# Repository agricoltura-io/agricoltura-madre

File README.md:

# agricoltura-madre
Wired and Wireless gateway for all Agricoltura sensors/module supports RS485, Sub1GHZ, and 2.4GHZ networks

Quick Specs:

Beaglebone Green Based Version - Cape
- Seeedstudio Beaglebone Green
- 2x RS485 ports
- Sub 1GHZ wirless modem with SMA Antenna Connector
- 2.4GHZ wireless modem with SMA Antenna connector, supporting all 2.4G types
- WiFi modem with SMA antenna connector
- 1x USB 2.0 ports
- USB serial monitor connection
- Ethernet

Beaglebone SiP Based Version
- OSD335x Family System-in-package, running Debian Linux
- 4x RS485 ports
- Sub 1GHZ wirless modem with SMA Antenna Connector
- 2.4GHZ wireless model with SMA Antenna connector, supporting all 2.4G types
- WiFi modem with SMA antenna connector
- 2X USB 2.0 ports
- USB serial monitor connection
- Ethernet

Raspberry Pi 4 based version:
- 2x RS485 ports
- Sub 1GHZ wirless modem with SMA Antenna Connector
- 2.4GHZ wireless model with SMA Antenna connector, supporting all 2.4G types
- Integrated WiFi (RPi4)
- USB ports (RPi4)
- Ethernet
- PoE or 24VAC Power

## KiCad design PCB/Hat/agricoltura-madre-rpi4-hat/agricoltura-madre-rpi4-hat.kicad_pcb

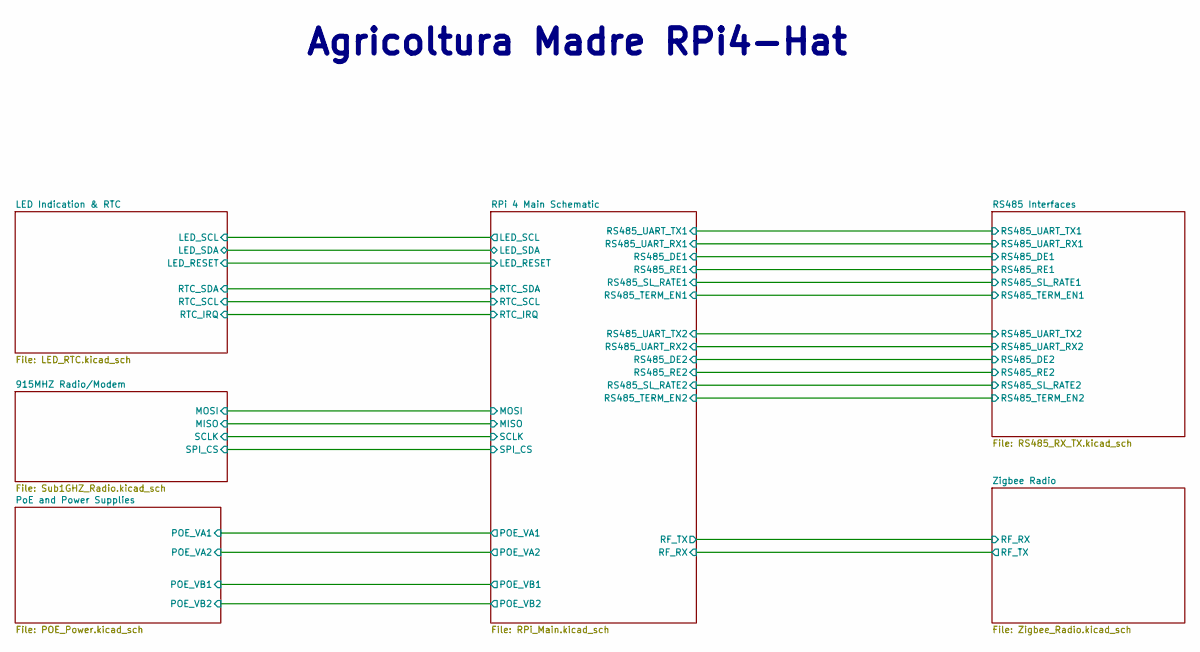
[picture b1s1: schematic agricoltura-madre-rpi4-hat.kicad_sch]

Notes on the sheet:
Agricoltura Madre RPi4-Hat

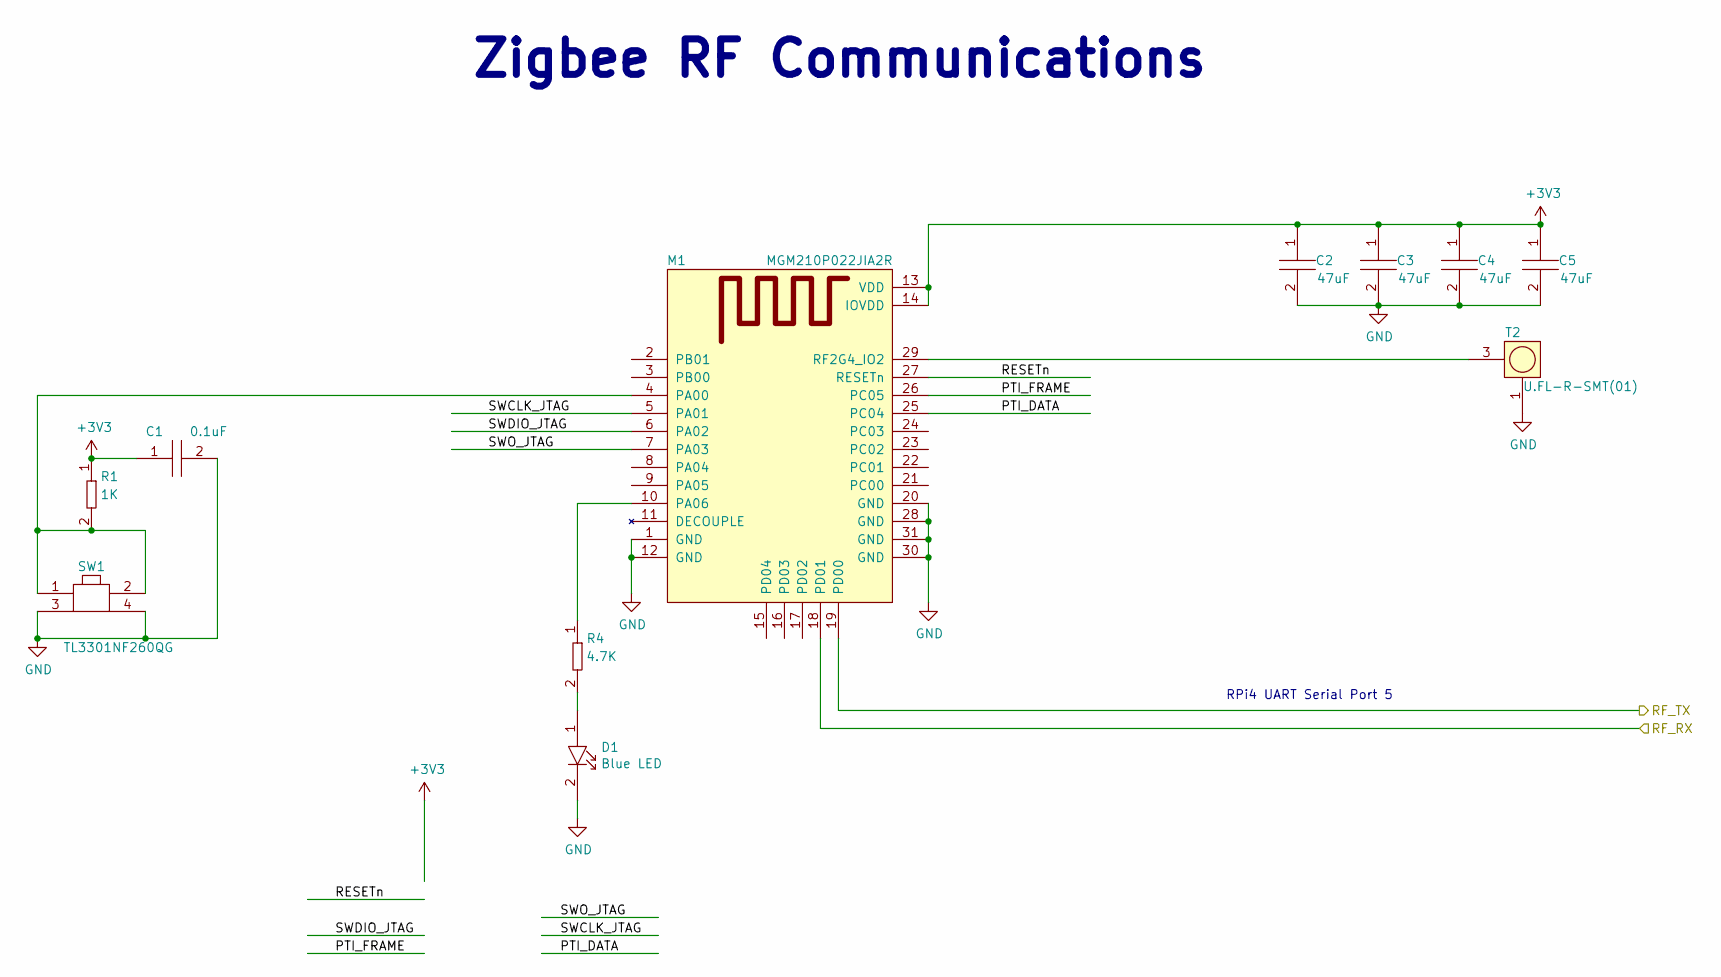
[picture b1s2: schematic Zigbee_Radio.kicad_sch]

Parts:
C1: GRM155R71E104KE14J; C0402; Tolerance 10%; Voltage 25V; MFR# GRM155R71E104KE14J
C2, C3, C4, C5: GRM188R60J476ME15D; C0603; Tolerance 20%; Voltage 6.3V; MFR# GRM188R60J476ME15D
D1: LTST-C194TBKT; LED0603; Tolerance *; Voltage 3.3V; MFR# LTST-C194TBKT
M1: MGM210P022JIA2R; Tolerance *; Voltage 1.8V-3.8V; MFR# MGM210P022JIA2R
R1: RC0402FR-071KL; R0402; Tolerance 1%; Voltage *; MFR# RC0402FR-071KL
R4: RC0402FR-074K7L; R0402; Tolerance 1%; Voltage *; MFR# RC0402FR-074K7L
SW1: TL3301NF260QG; Tolerance *; Voltage 12VDC; MFR# TL3301NF260QG
T2: U.FL-R-SMT(01); HRS_U.FL-R-SMT; Tolerance *; Voltage 3.3V; MFR# U.FL-R-SMT(01)

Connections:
+3V3: C1.1, C2.1, C3.1, C4.1, C5.1, M1.13 (VDD), M1.14 (IOVDD), R1.1; also elsewhere on the board
/RPi 4 Main Schematic/RF_RX: M1.19 (PD00); also elsewhere on the board
/Zigbee Radio /PTI_DATA: M1.25 (PC04)
/Zigbee Radio /PTI_FRAME: M1.26 (PC05)
/Zigbee Radio /RESETn: M1.27 (RESETn)
/Zigbee Radio /RF_RX: M1.18 (PD01); also elsewhere on the board
/Zigbee Radio /SWCLK_JTAG: M1.5 (PA01)
/Zigbee Radio /SWDIO_JTAG: M1.6 (PA02)
/Zigbee Radio /SWO_JTAG: M1.7 (PA03)
GND: C1.2, C2.2, C3.2, C4.2, C5.2, D1.2, M1.1 (GND), M1.12 (GND), M1.20 (GND), M1.28 (GND), M1.30 (GND), M1.31 (GND), SW1.3, SW1.4, T2.1; also elsewhere on the board
unnamed: D1.1, R4.2
unnamed: M1.4 (PA00), R1.2, SW1.1, SW1.2
unnamed: M1.10 (PA06), R4.1
unnamed: M1.29 (RF2G4_IO2), T2.3

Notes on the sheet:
Zigbee RF Communications
RPi4 UART Serial Port 5

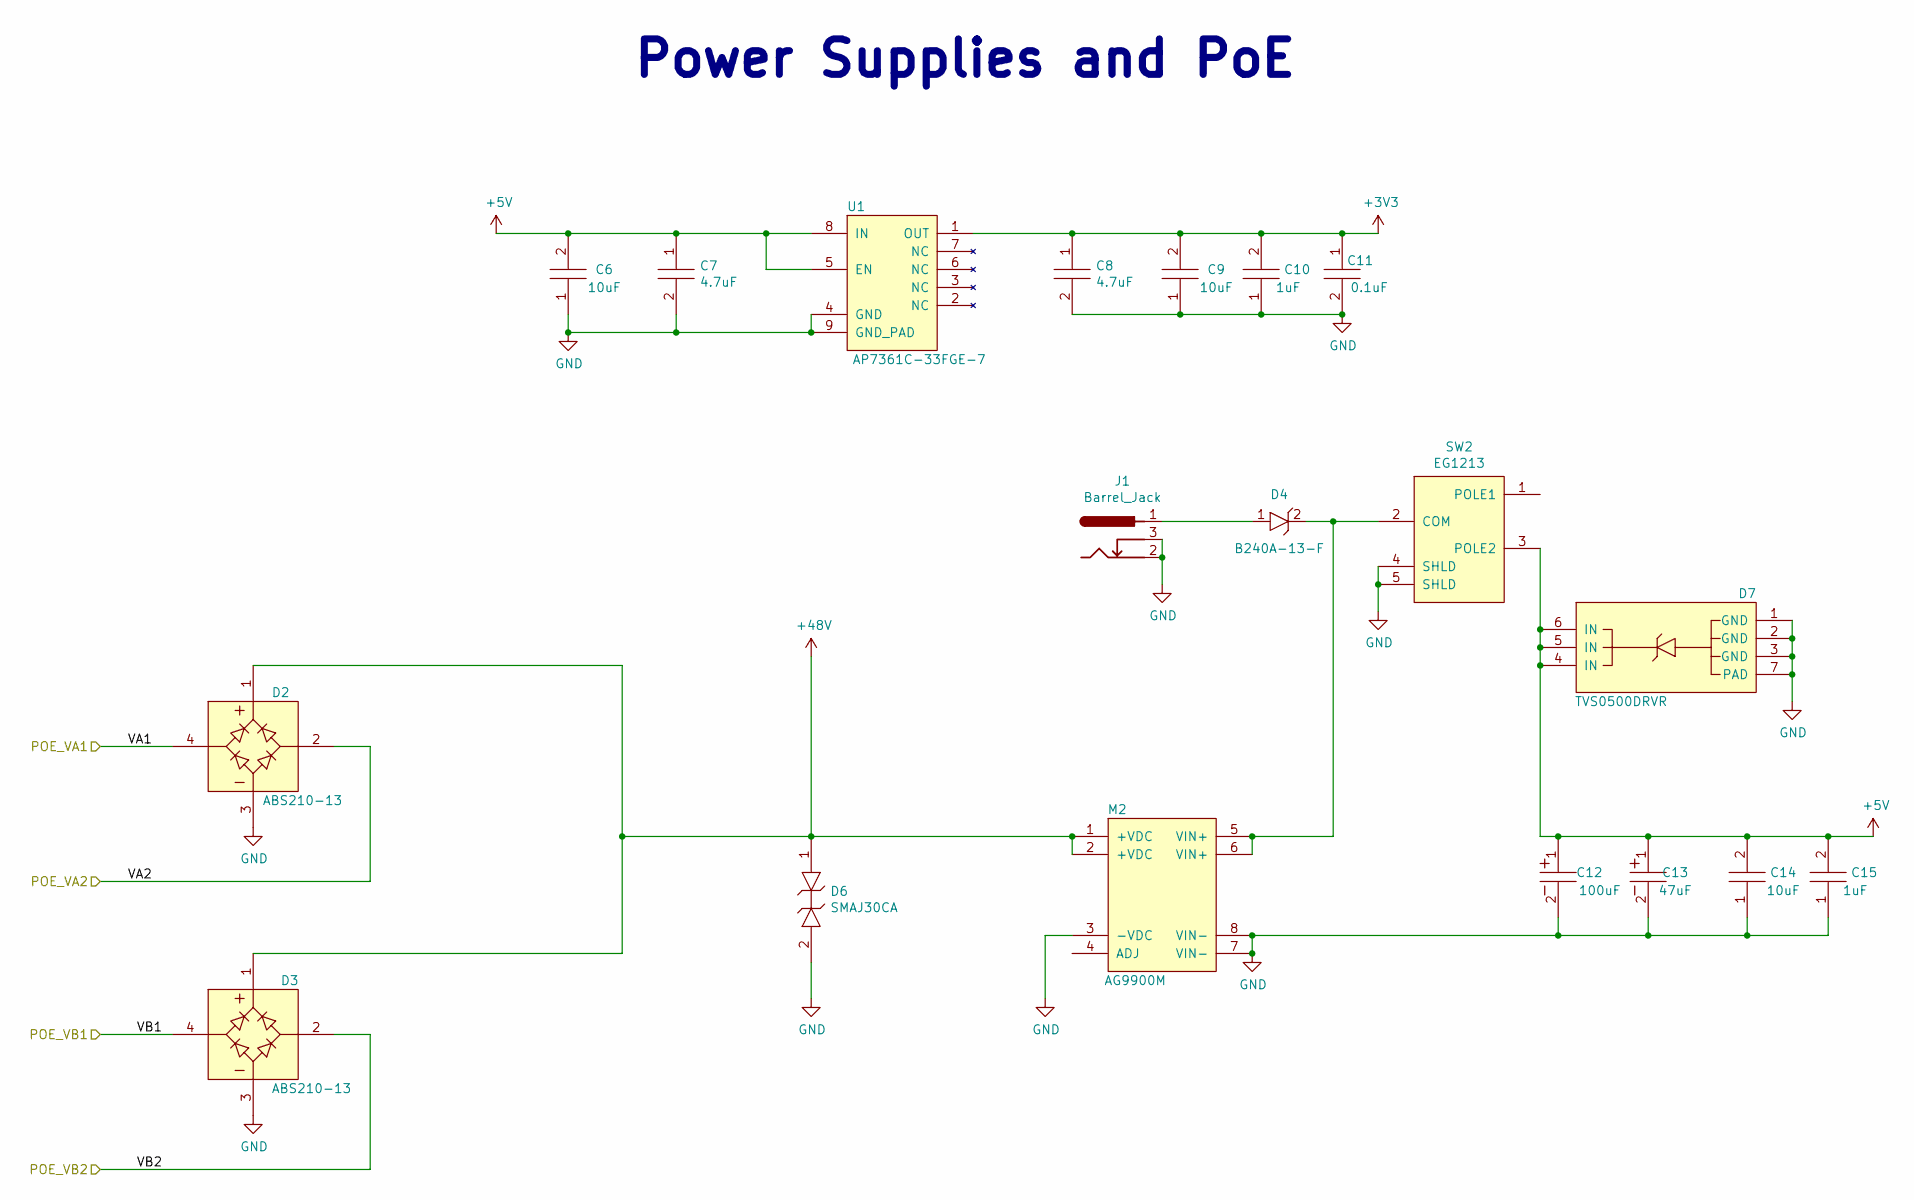
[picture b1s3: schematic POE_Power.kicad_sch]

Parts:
C6, C9, C14: GRM188R61A106KE69J; C0603; Tolerance 10%; Voltage 10V; MFR# GRM188R61A106KE69J
C7, C8: GRM155R61A475MEAAD; C0402; Tolerance 20%; Voltage 10V; MFR# GRM155R61A475MEAAD
C10, C15: GRM155C81A105KA12D; C0402; Tolerance 10%; Voltage 10V; MFR# GRM155C81A105KA12D
C11: GRM155R71E104KE14J; C0402; Tolerance 10%; Voltage 25V; MFR# GRM155R71E104KE14J
C12: UUX1J101MNL1GS; Tolerance 20%; Voltage 63V; MFR# UUX1J101MNL1GS
C13: UWT1H470MCL1GS; Tolerance 20%; Voltage 63V; MFR# UWT1H470MCL1GS
D2, D3: ABS210-13; Tolerance *; Voltage 1KV 2A; MFR# ABS210-13
D4: B240A-13-F; Tolerance *; Voltage 40V; MFR# B240A-13-F
D6: SMAJ30CA; Tolerance *; Voltage 48.4V; MFR# SMAJ30CA
D7: TVS0500DRVR; Tolerance *; Voltage 5V; MFR# TVS0500DRVR
J1: Barrel_Jack; BARREL_JACK
M2: AG9900M; 9900M_POE; Tolerance *; Voltage *; MFR# *
SW2: EG1213; SW_EG1213; Tolerance *; Voltage 30V; MFR# EG1213
U1: AP7361C-33FGE-7; DFN3030-8; Tolerance *; Voltage 6VIN MAX 3.3V out; MFR# AP7361C-33FGE-7

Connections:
+3V3: C8.1, C9.2, C10.2, C11.1, U1.1 (OUT); also elsewhere on the board
+5V: C6.2, C7.1, C12.1, C13.1, C14.2, C15.2, D7.4 (IN), D7.5 (IN), D7.6 (IN), SW2.3 (POLE2), U1.5 (EN), U1.8 (IN); also elsewhere on the board
+48V: D2.1, D3.1, D6.1, M2.1 (+VDC), M2.2 (+VDC)
/PoE and Power Supplies/POE_VA1: D2.4; also elsewhere on the board
/PoE and Power Supplies/POE_VA2: D2.2; also elsewhere on the board
/PoE and Power Supplies/POE_VB1: D3.4; also elsewhere on the board
/PoE and Power Supplies/POE_VB2: D3.2; also elsewhere on the board
GND: C6.1, C7.2, C8.2, C9.1, C10.1, C11.2, C12.2, C13.2, C14.1, C15.1, D2.3, D3.3, D6.2, D7.1 (GND), D7.2 (GND), D7.3 (GND), D7.7 (PAD), J1.2, J1.3, M2.3 (-VDC), M2.7 (VIN-), M2.8 (VIN-), SW2.4 (SHLD), SW2.5 (SHLD), U1.4 (GND), U1.9 (GND_PAD); also elsewhere on the board
unnamed: D4.1, J1.1
unnamed: D4.2, M2.5 (VIN+), M2.6 (VIN+), SW2.2 (COM)

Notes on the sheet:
Power Supplies and PoE

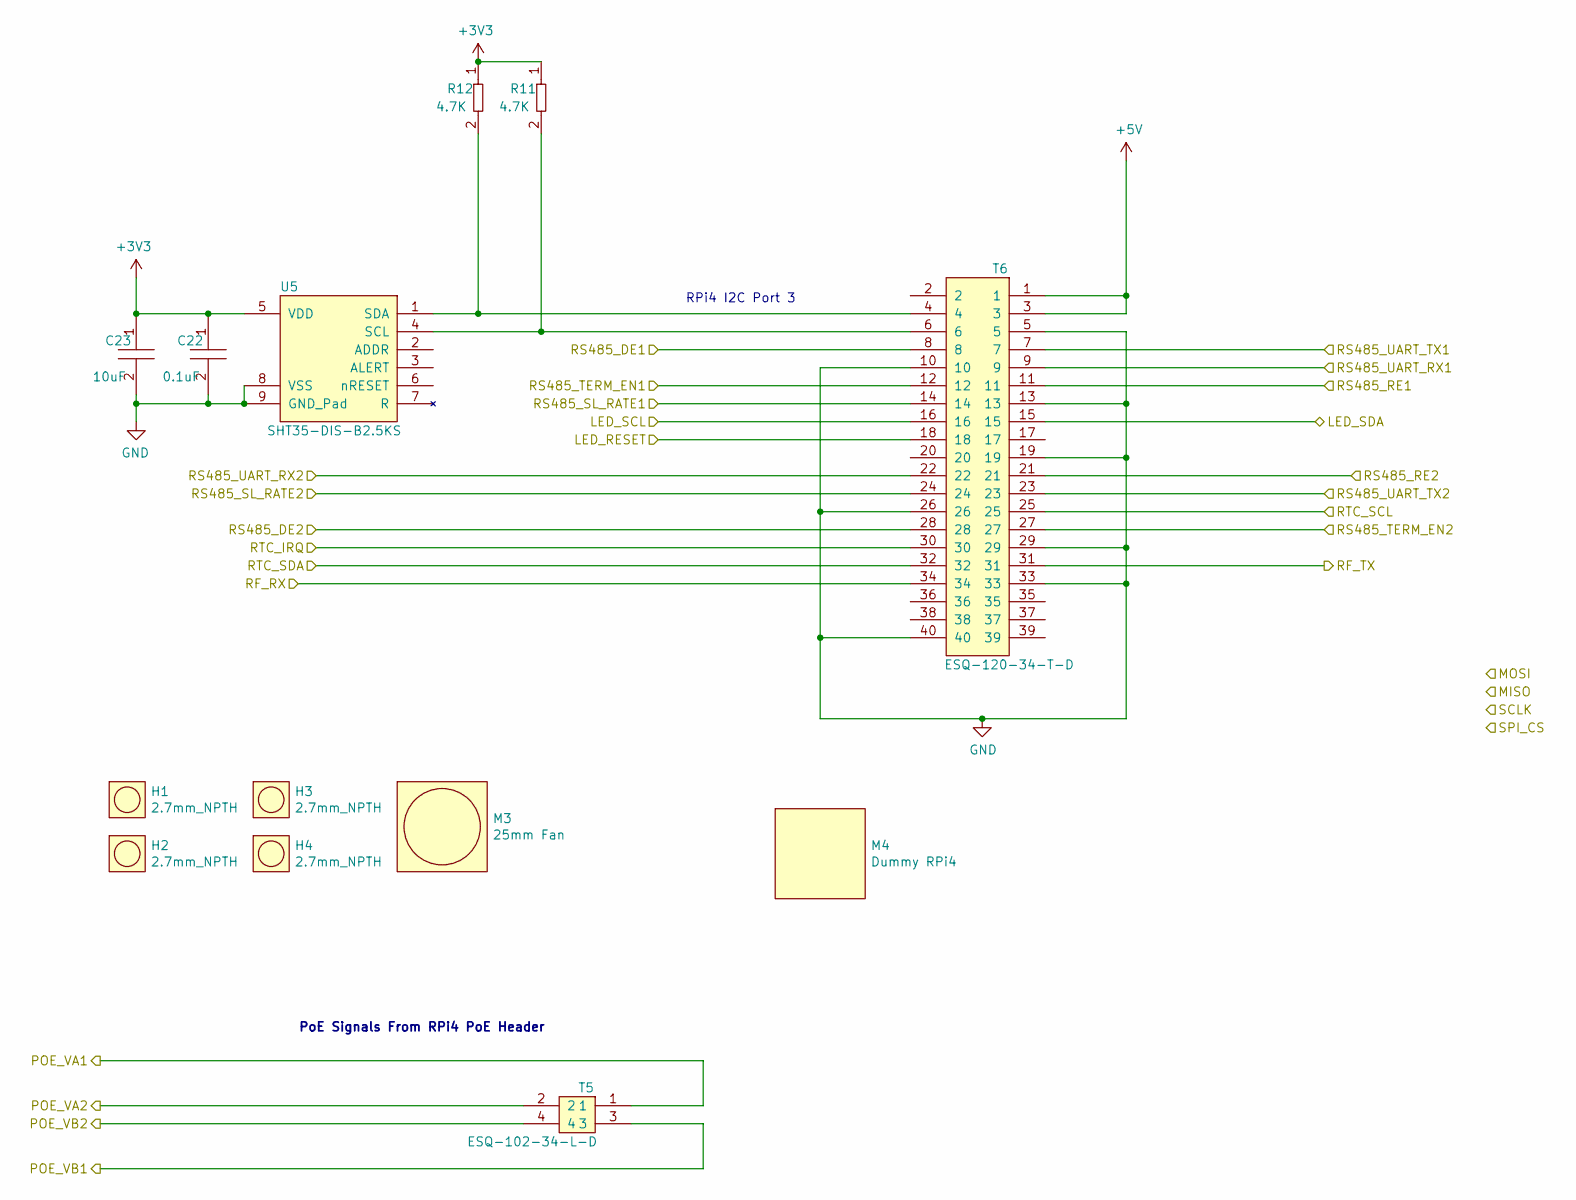
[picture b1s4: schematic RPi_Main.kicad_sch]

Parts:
C22: GRM155R71E104KE14J; C0402; Tolerance 10%; Voltage 25V; MFR# GRM155R71E104KE14J
C23: GRM188R61A106KE69J; C0603; Tolerance 10%; Voltage 10V; MFR# GRM188R61A106KE69J
H1, H2, H3, H4: 2.7mm_NPTH; Tolerance *; Voltage *; MFR# *
M3: 25mm_FAN; Tolerance *; Voltage *; MFR# *
M4: DummyPi; RPi4_SHAPE_3D; Tolerance *; Voltage *; MFR# *
R11, R12: RC0402FR-074K7L; R0402; Tolerance 1%; Voltage *; MFR# RC0402FR-074K7L
T5: ESQ-102-34-L-D; Tolerance *; Voltage 550VAC; MFR# ESQ-102-34-L-D
T6: ESQ-120-34-T-D; ESQ-120-34-T-D_2x20_Pitch2.54mm; Tolerance *; Voltage 550VAC; MFR# ESQ-120-34-T-D
U5: SHT35-DIS-B2.5KS; DFN8_SHT35; Tolerance *; Voltage 2.15V-5.5V; MFR# SHT35-DIS-B2.5KS

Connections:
+3V3: C22.1, C23.1, R11.1, R12.1, U5.5 (VDD); also elsewhere on the board
+5V: T6.1, T6.3; also elsewhere on the board
/LED Indication & RTC/LED_RESET: T6.18; also elsewhere on the board
/LED Indication & RTC/LED_SCL: T6.16; also elsewhere on the board
/LED Indication & RTC/LED_SDA: T6.15; also elsewhere on the board
/LED Indication & RTC/RTC_IRQ: T6.30; also elsewhere on the board
/LED Indication & RTC/RTC_SCL: T6.25; also elsewhere on the board
/LED Indication & RTC/RTC_SDA: T6.32; also elsewhere on the board
/PoE and Power Supplies/POE_VA1: T5.1; also elsewhere on the board
/PoE and Power Supplies/POE_VA2: T5.2; also elsewhere on the board
/PoE and Power Supplies/POE_VB1: T5.3; also elsewhere on the board
/PoE and Power Supplies/POE_VB2: T5.4; also elsewhere on the board
/RPi 4 Main Schematic/RF_RX: T6.34; also elsewhere on the board
/RPi 4 Main Schematic/RS485_DE1: T6.8; also elsewhere on the board
/RPi 4 Main Schematic/RS485_DE2: T6.28; also elsewhere on the board
/RPi 4 Main Schematic/RS485_RE1: T6.11; also elsewhere on the board
/RPi 4 Main Schematic/RS485_RE2: T6.21; also elsewhere on the board
/RPi 4 Main Schematic/RS485_SL_RATE1: T6.14; also elsewhere on the board
/RPi 4 Main Schematic/RS485_SL_RATE2: T6.24; also elsewhere on the board
/RPi 4 Main Schematic/RS485_TERM_EN1: T6.12; also elsewhere on the board
/RPi 4 Main Schematic/RS485_TERM_EN2: T6.27; also elsewhere on the board
/RPi 4 Main Schematic/RS485_UART_RX1: T6.9; also elsewhere on the board
/RPi 4 Main Schematic/RS485_UART_RX2: T6.22; also elsewhere on the board
/RPi 4 Main Schematic/RS485_UART_TX1: T6.7; also elsewhere on the board
/RPi 4 Main Schematic/RS485_UART_TX2: T6.23; also elsewhere on the board
/Zigbee Radio /RF_RX: T6.31; also elsewhere on the board
GND: C22.2, C23.2, T6.5, T6.10, T6.13, T6.19, T6.26, T6.29, T6.33, T6.40, U5.8 (VSS), U5.9 (GND_Pad); also elsewhere on the board
unnamed: R11.2, T6.6, U5.4 (SCL)
unnamed: R12.2, T6.4, U5.1 (SDA)

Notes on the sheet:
PoE Signals From RPi4 PoE Header
RPi4 I2C Port 3

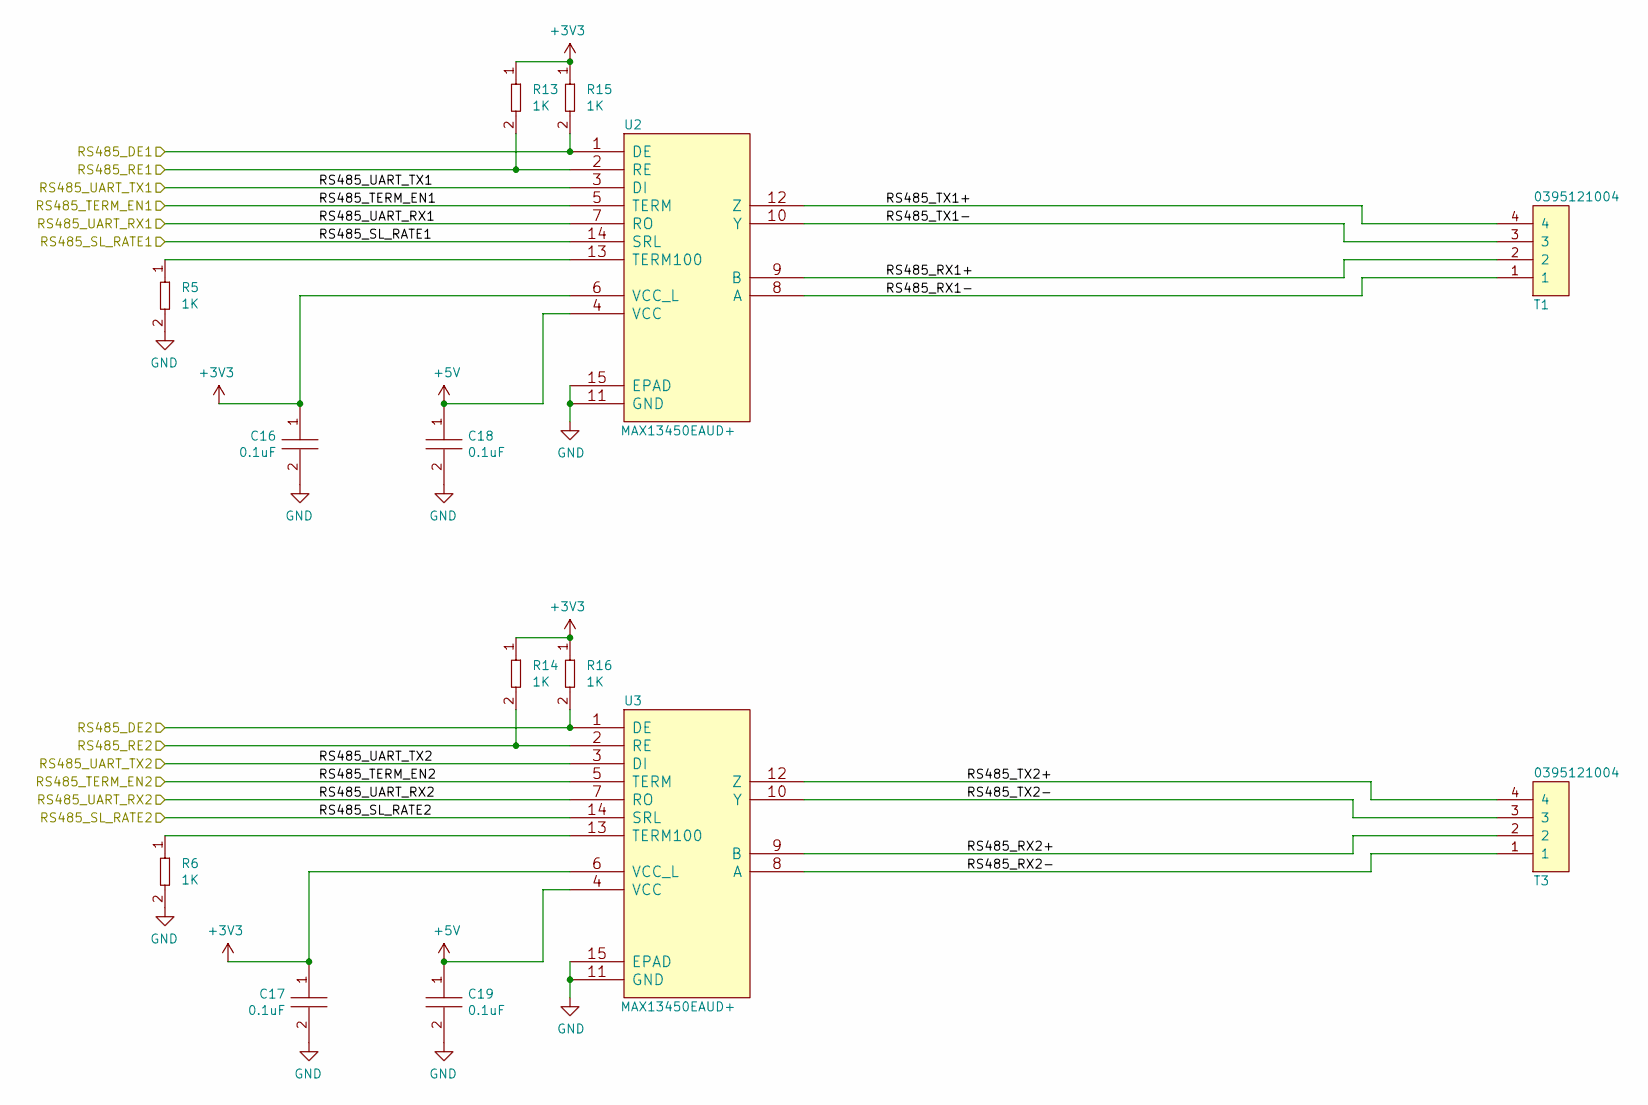
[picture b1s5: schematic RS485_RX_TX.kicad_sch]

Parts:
C16, C17: C0402C104K9PACTU; R0402; Tolerance 10%; Voltage 6.3V; MFR# C0402C104K9PACTU
C18, C19: CGA3E2X7R1H104K080AA; C0603; Tolerance 10%; Voltage 50V; MFR# CGA3E2X7R1H104K080AA
R5, R6, R13, R14, R15, R16: RC0402FR-071KL; R0402; Tolerance 1%; Voltage *; MFR# RC0402FR-071KL
T1, T3: 0395121004; Tolerance *; Voltage 300V; MFR# 0395121004
U2, U3: MAX13450EAUD+; MAX13450EAUD&plus_; Tolerance *; Voltage 4.75V ~ 5.25V; MFR# MAX13450EAUD+

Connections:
+3V3: C16.1, C17.1, R13.1, R14.1, R15.1, R16.1, U2.6 (VCC_L), U3.6 (VCC_L); also elsewhere on the board
+5V: C18.1, C19.1, U2.4 (VCC), U3.4 (VCC); also elsewhere on the board
/RPi 4 Main Schematic/RS485_DE1: R15.2, U2.1 (DE); also elsewhere on the board
/RPi 4 Main Schematic/RS485_DE2: R16.2, U3.1 (DE); also elsewhere on the board
/RPi 4 Main Schematic/RS485_RE1: R13.2, U2.2 (RE); also elsewhere on the board
/RPi 4 Main Schematic/RS485_RE2: R14.2, U3.2 (RE); also elsewhere on the board
/RPi 4 Main Schematic/RS485_SL_RATE1: U2.14 (SRL); also elsewhere on the board
/RPi 4 Main Schematic/RS485_SL_RATE2: U3.14 (SRL); also elsewhere on the board
/RPi 4 Main Schematic/RS485_TERM_EN1: U2.5 (TERM); also elsewhere on the board
/RPi 4 Main Schematic/RS485_TERM_EN2: U3.5 (TERM); also elsewhere on the board
/RPi 4 Main Schematic/RS485_UART_RX1: U2.7 (RO); also elsewhere on the board
/RPi 4 Main Schematic/RS485_UART_RX2: U3.7 (RO); also elsewhere on the board
/RPi 4 Main Schematic/RS485_UART_TX1: U2.3 (DI); also elsewhere on the board
/RPi 4 Main Schematic/RS485_UART_TX2: U3.3 (DI); also elsewhere on the board
/RS485 Interfaces/RS485_RX1+: T1.2, U2.9 (B)
/RS485 Interfaces/RS485_RX1-: T1.1, U2.8 (A)
/RS485 Interfaces/RS485_RX2+: T3.2, U3.9 (B)
/RS485 Interfaces/RS485_RX2-: T3.1, U3.8 (A)
/RS485 Interfaces/RS485_TX1+: T1.4, U2.12 (Z)
/RS485 Interfaces/RS485_TX1-: T1.3, U2.10 (Y)
/RS485 Interfaces/RS485_TX2+: T3.4, U3.12 (Z)
/RS485 Interfaces/RS485_TX2-: T3.3, U3.10 (Y)
GND: C16.2, C17.2, C18.2, C19.2, R5.2, R6.2, U2.11 (GND), U2.15 (EPAD), U3.11 (GND), U3.15 (EPAD); also elsewhere on the board
unnamed: R5.1, U2.13 (TERM100)
unnamed: R6.1, U3.13 (TERM100)

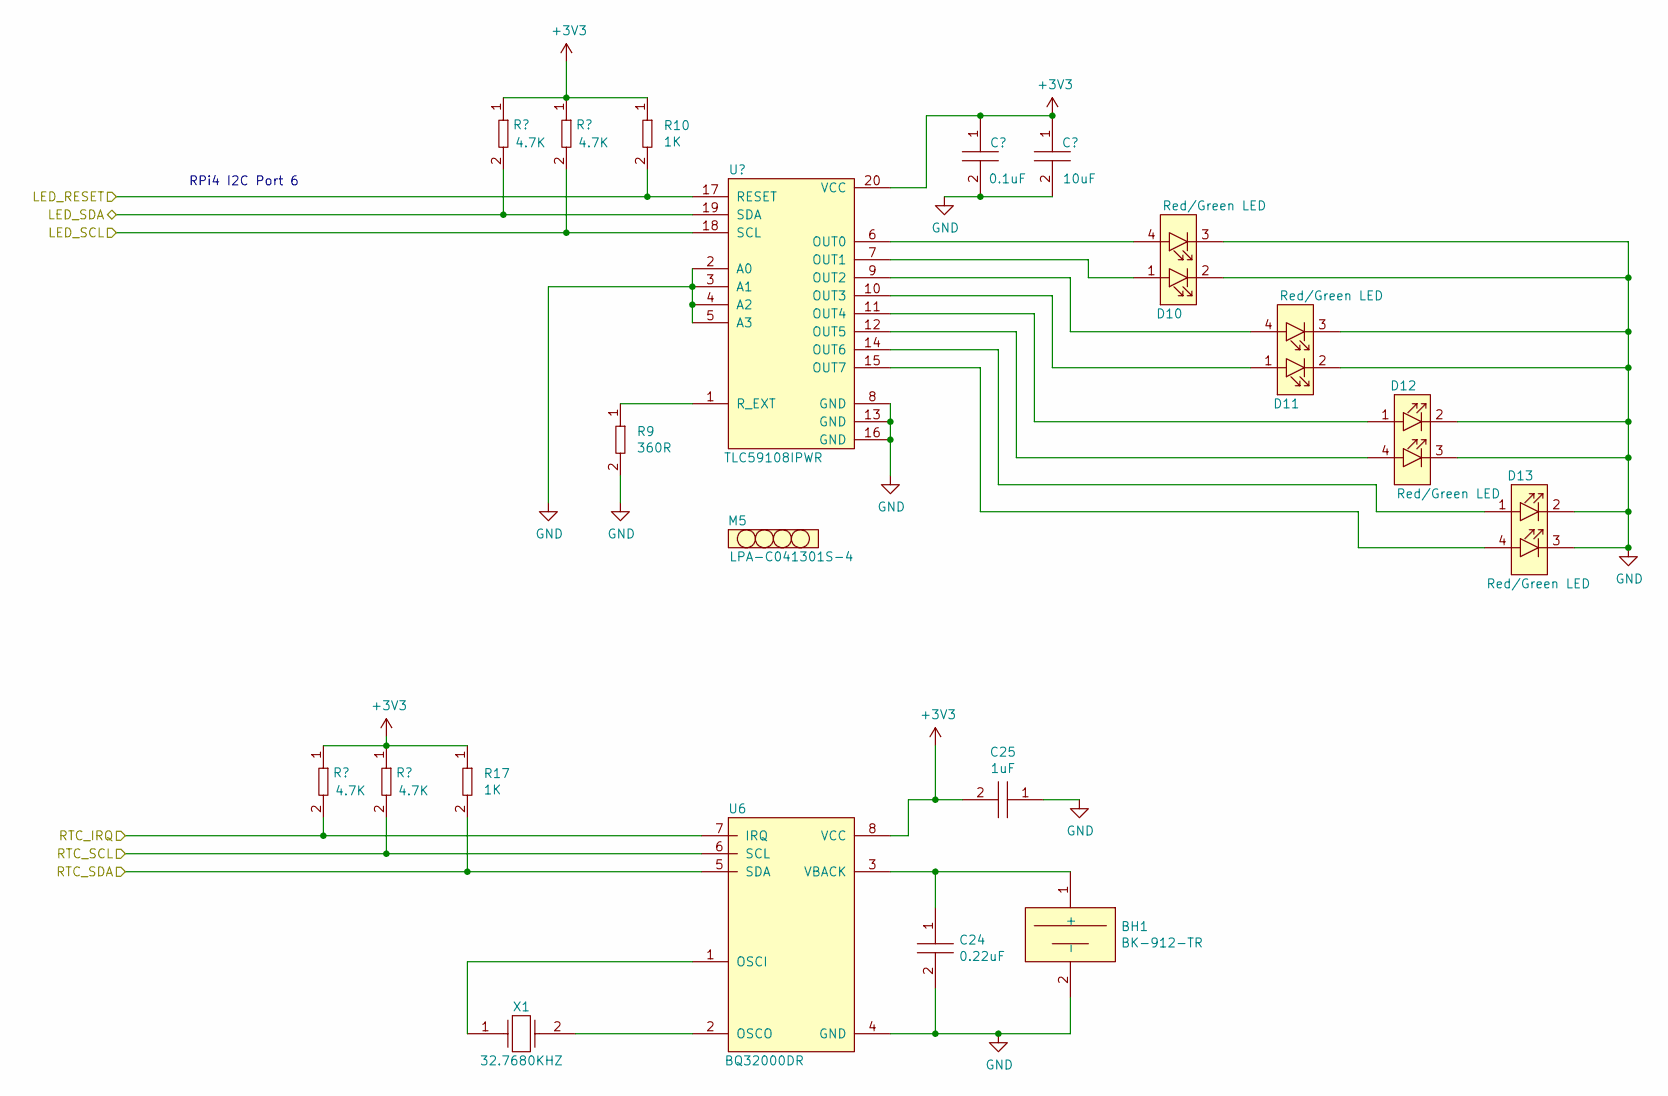
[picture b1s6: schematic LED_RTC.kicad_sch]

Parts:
BH1: BK-912-TR; BK-912; Tolerance *; Voltage 3V; MFR# BK-912-TR
C20: GRM155R71E104KE14J; C0402; Tolerance 10%; Voltage 25V; MFR# GRM155R71E104KE14J
C21: GRM188R61A106KE69J; C0603; Tolerance 10%; Voltage 10V; MFR# GRM188R61A106KE69J
C24: GRM155R71A224KE01D; C0402; Tolerance 10%; Voltage 10V; MFR# GRM155R71A224KE01D
C25: GRM155C81A105KA12D; C0402; Tolerance 10%; Voltage 10V; MFR# GRM155C81A105KA12D
D10, D11, D12, D13: APHBM2012SURKCGKC; LED_APHBM2012SURKCGKC; Tolerance *; Voltage 2.1V/1.95V; MFR# APHBM2012SURKCGKC
M5: LPA-C041301S-4; Tolerance *; Voltage *; MFR# LPA-C041301S-4
R2, R3, R7, R8: RC0402FR-074K7L; R0402; Tolerance 1%; Voltage *; MFR# RC0402FR-074K7L
R9: RC0402FR-07360RL; R0402; Tolerance 1%; Voltage *; MFR# RC0402FR-07360RL
R10, R17: RC0402FR-071KL; R0402; Tolerance 1%; Voltage *; MFR# RC0402FR-071KL
U4: TLC59108IPWR; 20TSSOP_Ti_PWR; Tolerance *; Voltage 3-5.5V IN, 17V OUT; MFR# Texas Instruments
U6: BQ32000DR; Tolerance *; Voltage 3.3V; MFR# IC RTC CLK/CALENDAR I2C 8-SOIC
X1: ECS-.327-12.5-34B-TR; Tolerance *; Voltage *; MFR# ECS-.327-12.5-34B-TR

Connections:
+3V3: C20.1, C21.1, C25.2, R2.1, R3.1, R7.1, R8.1, R10.1, R17.1, U4.20 (VCC), U6.8 (VCC); also elsewhere on the board
/LED Indication & RTC/LED_RESET: R10.2, U4.17 (RESET); also elsewhere on the board
/LED Indication & RTC/LED_SCL: R8.2, U4.18 (SCL); also elsewhere on the board
/LED Indication & RTC/LED_SDA: R7.2, U4.19 (SDA); also elsewhere on the board
/LED Indication & RTC/RTC_IRQ: R2.2, U6.7 (IRQ); also elsewhere on the board
/LED Indication & RTC/RTC_SCL: R3.2, U6.6 (SCL); also elsewhere on the board
/LED Indication & RTC/RTC_SDA: R17.2, U6.5 (SDA); also elsewhere on the board
GND: BH1.2 (-), C20.2, C21.2, C24.2, C25.1, D10.2, D10.3, D11.2, D11.3, D12.2, D12.3, D13.2, D13.3, R9.2, U4.2 (A0), U4.3 (A1), U4.4 (A2), U4.5 (A3), U4.8 (GND), U4.13 (GND), U4.16 (GND), U6.4 (GND); also elsewhere on the board
unnamed: BH1.1 (+), C24.1, U6.3 (VBACK)
unnamed: D10.1, U4.7 (OUT1)
unnamed: D10.4, U4.6 (OUT0)
unnamed: D11.1, U4.10 (OUT3)
unnamed: D11.4, U4.9 (OUT2)
unnamed: D12.1, U4.11 (OUT4)
unnamed: D12.4, U4.12 (OUT5)
unnamed: D13.1, U4.14 (OUT6)
unnamed: D13.4, U4.15 (OUT7)
unnamed: R9.1, U4.1 (R_EXT)
unnamed: U6.1 (OSCI), X1.1
unnamed: U6.2 (OSCO), X1.2

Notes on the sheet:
RPi4 I2C Port 6

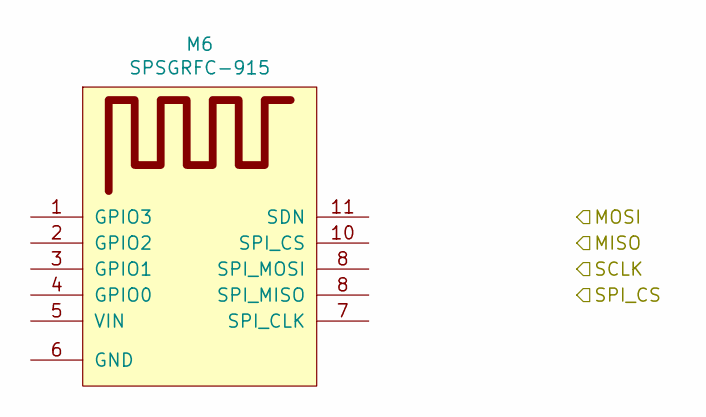
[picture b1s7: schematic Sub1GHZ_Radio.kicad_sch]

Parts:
M6: SPSGRFC-915; XCVR_SPSGRF-915; Tolerance *; Voltage 1.8V ~ 3.6V; MFR# SPSGRFC-915

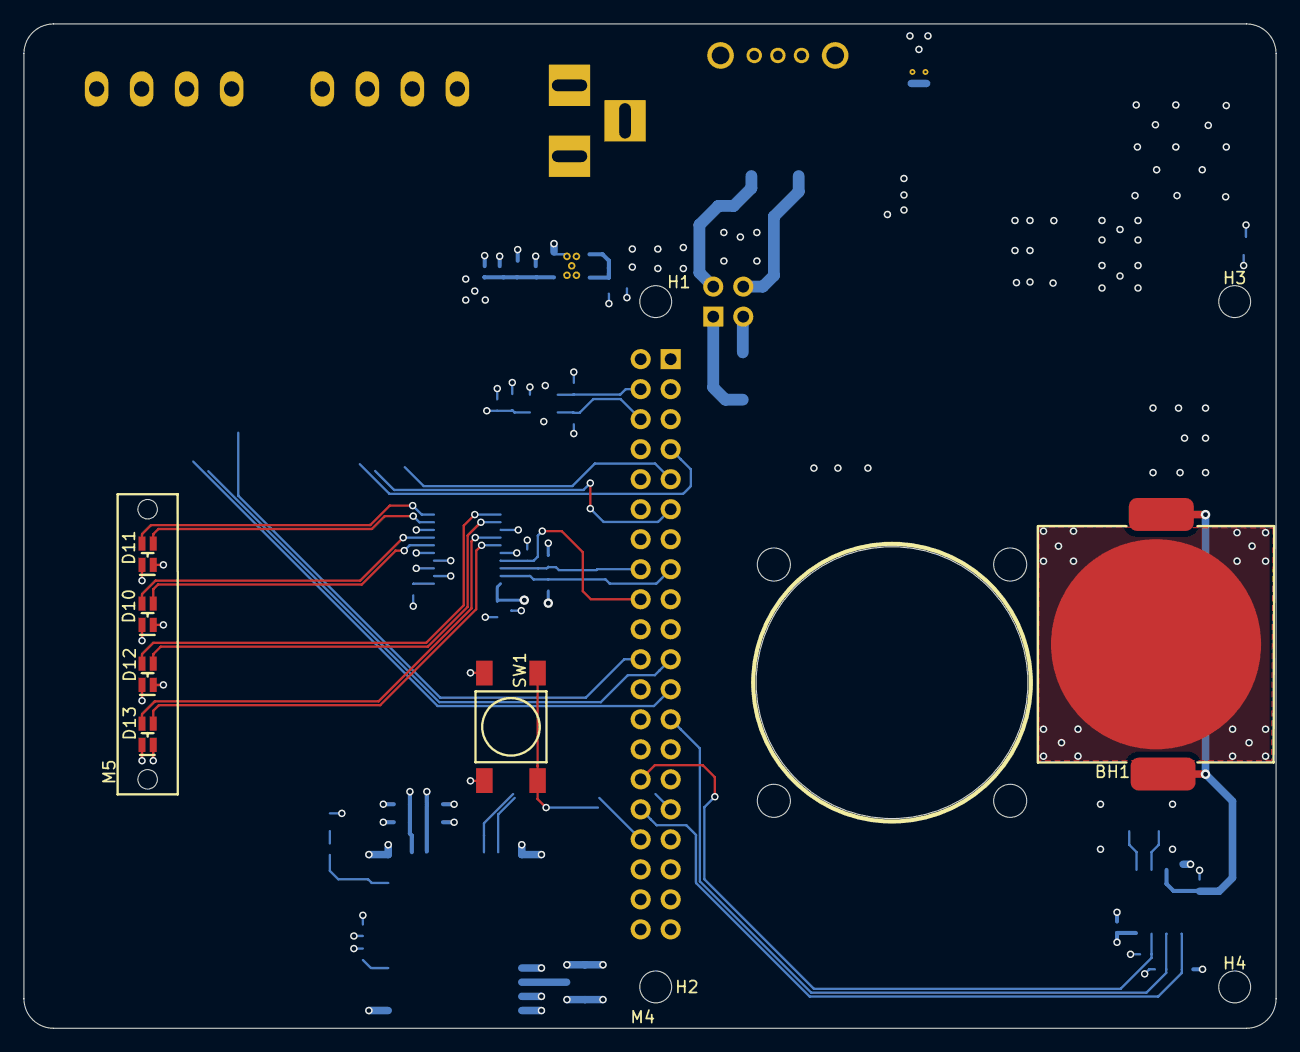
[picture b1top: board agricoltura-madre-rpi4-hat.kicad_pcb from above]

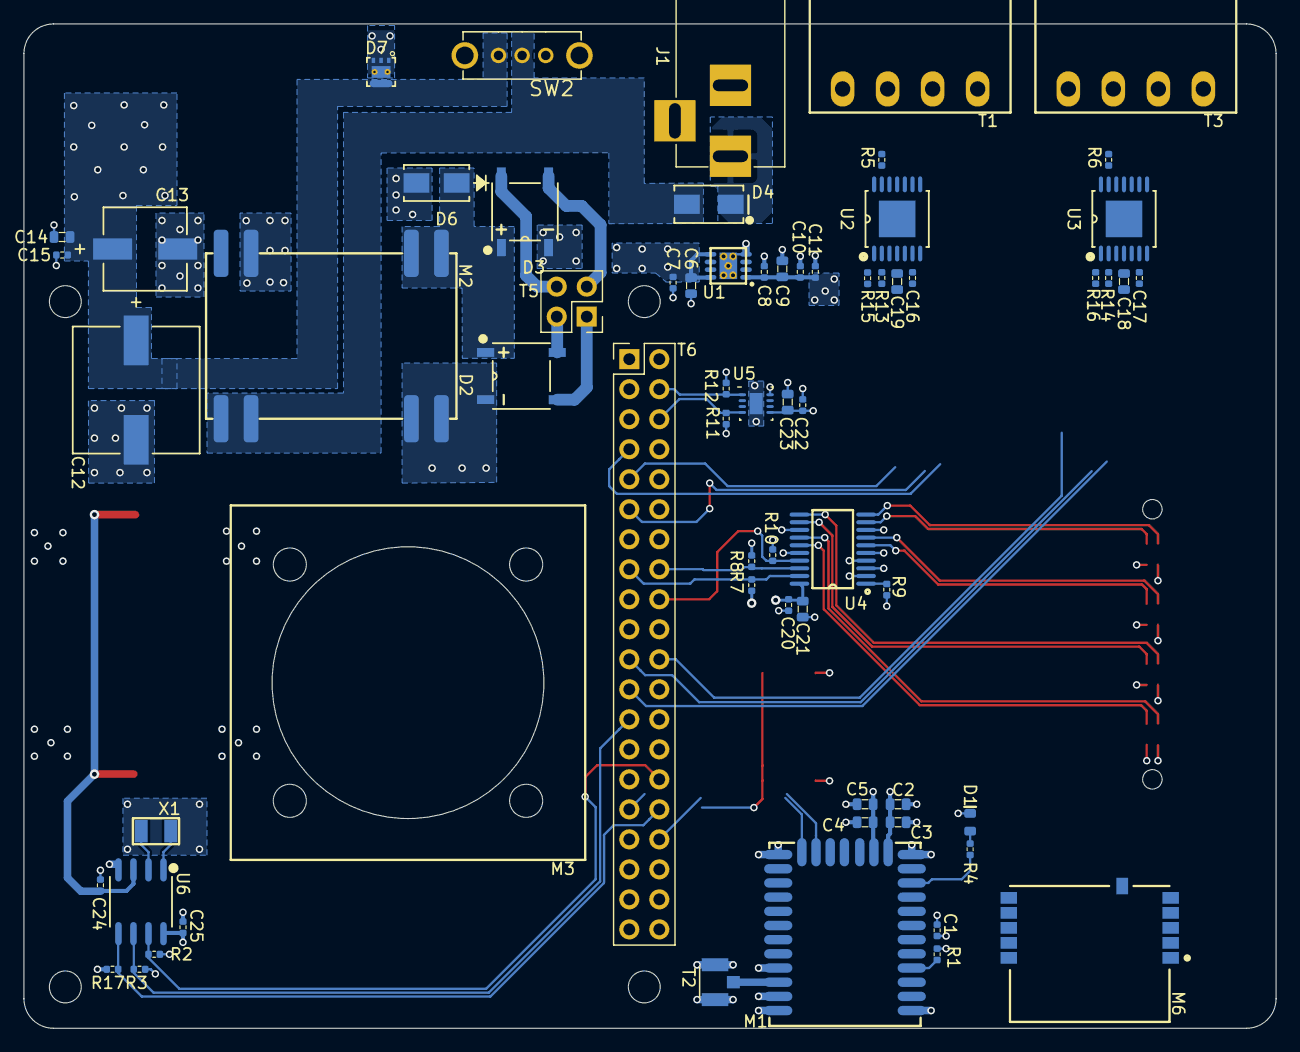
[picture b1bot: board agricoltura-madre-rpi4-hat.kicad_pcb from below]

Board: 4 copper layers, 106.0 x 85.0 mm, 78 parts (66 on the bottom side), 58 nets.

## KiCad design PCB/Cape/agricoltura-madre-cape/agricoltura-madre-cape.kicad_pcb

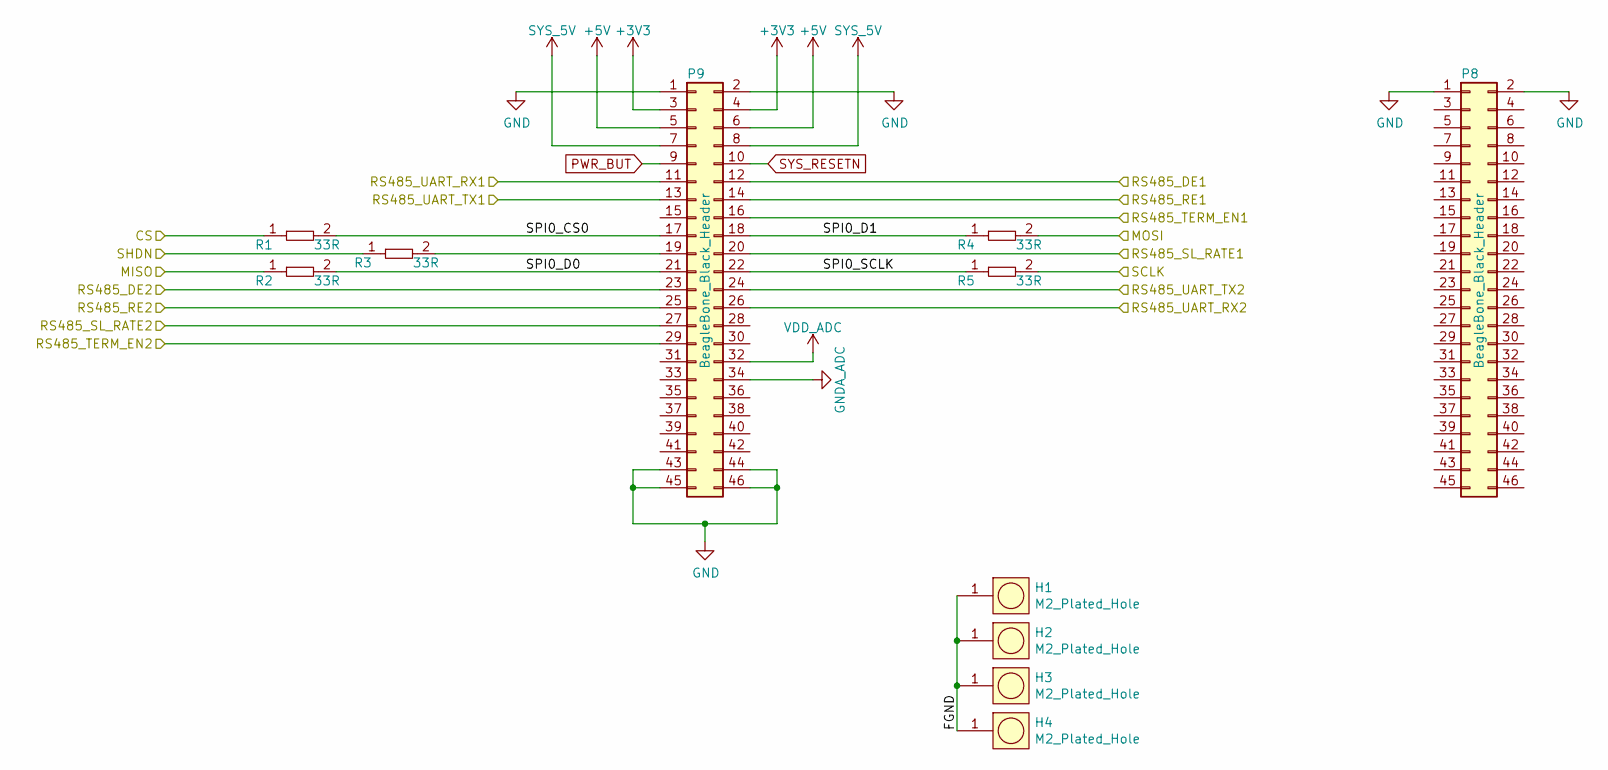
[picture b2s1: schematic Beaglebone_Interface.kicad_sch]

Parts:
H1, H2, H3, H4: M2_Plated_Hole; M2_HOLE; Tolerance *; Voltage *; MFR# *
P8, P9: BeagleBone_Black_Header; Socket_BeagleBone_Black
R1, R2, R3, R4, R5: RC0402FR-0733RL; R0402; Tolerance 1%; Voltage *; MFR# RC0402FR-0733RL

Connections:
+3V3: P9.3, P9.4; also elsewhere on the board
+5V: P9.5, P9.6; also elsewhere on the board
/915MHZ Radio/Modem/CS: R1.1; also elsewhere on the board
/915MHZ Radio/Modem/MISO: R2.1; also elsewhere on the board
/915MHZ Radio/Modem/MOSI: R4.2
/915MHZ Radio/Modem/SCLK: R5.2; also elsewhere on the board
/915MHZ Radio/Modem/SHDN: R3.1; also elsewhere on the board
/Beaglebone Interface/FGND: H1.1, H2.1, H3.1, H4.1
/Beaglebone Interface/RS485_DE1: P9.12; also elsewhere on the board
/Beaglebone Interface/RS485_DE2: P9.23; also elsewhere on the board
/Beaglebone Interface/RS485_RE1: P9.14; also elsewhere on the board
/Beaglebone Interface/RS485_RE2: P9.25; also elsewhere on the board
/Beaglebone Interface/RS485_SL_RATE1: P9.20; also elsewhere on the board
/Beaglebone Interface/RS485_SL_RATE2: P9.27; also elsewhere on the board
/Beaglebone Interface/RS485_TERM_EN1: P9.16; also elsewhere on the board
/Beaglebone Interface/RS485_TERM_EN2: P9.29; also elsewhere on the board
/Beaglebone Interface/RS485_UART_RX1: P9.11; also elsewhere on the board
/Beaglebone Interface/RS485_UART_RX2: P9.26; also elsewhere on the board
/Beaglebone Interface/RS485_UART_TX1: P9.13; also elsewhere on the board
/Beaglebone Interface/RS485_UART_TX2: P9.24; also elsewhere on the board
/Beaglebone Interface/SPI0_CS0: P9.17, R1.2
/Beaglebone Interface/SPI0_D0: P9.21, R2.2
/Beaglebone Interface/SPI0_D1: P9.18, R4.1
/Beaglebone Interface/SPI0_SCLK: P9.22, R5.1
GND: P8.1, P8.2, P9.1, P9.2, P9.43, P9.44, P9.45, P9.46; also elsewhere on the board
GNDA_ADC: P9.34
unnamed: P9.19, R3.2
PWR_BUT: P9.9
SYS_5V: P9.7, P9.8
SYS_RESETN: P9.10
VDD_ADC: P9.32

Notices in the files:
parts and their libraries:
Copyright 2016 Accelerated Designs. All rights reserved.
